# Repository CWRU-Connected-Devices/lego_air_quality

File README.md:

# LEGO Air Quality Monitor

An educational STEM kit developed by the Case Western Reserve University Institute for Smart, Secure and
Connected Systems (ISSACS). Participants build a working model of an optical air quality sensor using LEGO
bricks, custom electronics, and a Raspberry Pi Pico.

## What It Teaches

Real-world air quality monitors measure particulate matter (PM) by shining light through air and detecting
how much is scattered by particles. This kit builds a physical model of that principle: a LEGO brick
structure channels water vapor between a white LED and a photoreceptor. As vapor density changes, so does
the light reaching the sensor — just as particles would affect a real PM sensor. An 8-LED bar graph
displays the relative reading in real time.

## Repository Contents

- **`firmware/`** — MicroPython source code for the Raspberry Pi Pico
- **`legos/`** — 3D-printable LEGO-compatible brick designs (STL files + BrickLink Studio layout)
- **`pcb/`** — PCB design files (Eagle source, schematic PDF, Gerbers for fabrication)
- **`docs/`** — Documentation for kit builders, instructors, and participants
- **`images/`** — Reference photos used in documentation

## Attribution

This project is free to use and adapt under the MIT License. If you use these materials in your program,
we ask that you credit **CWRU ISSACS** and include our logo on participant-facing materials.

## License

MIT License — Copyright (c) 2021 Case Western Reserve University Institute for Smart, Secure and Connected
Systems. See [LICENSE](LICENSE) for details.

---

LEGO is a trademark of the LEGO Group, which does not sponsor, authorize, or endorse this project.

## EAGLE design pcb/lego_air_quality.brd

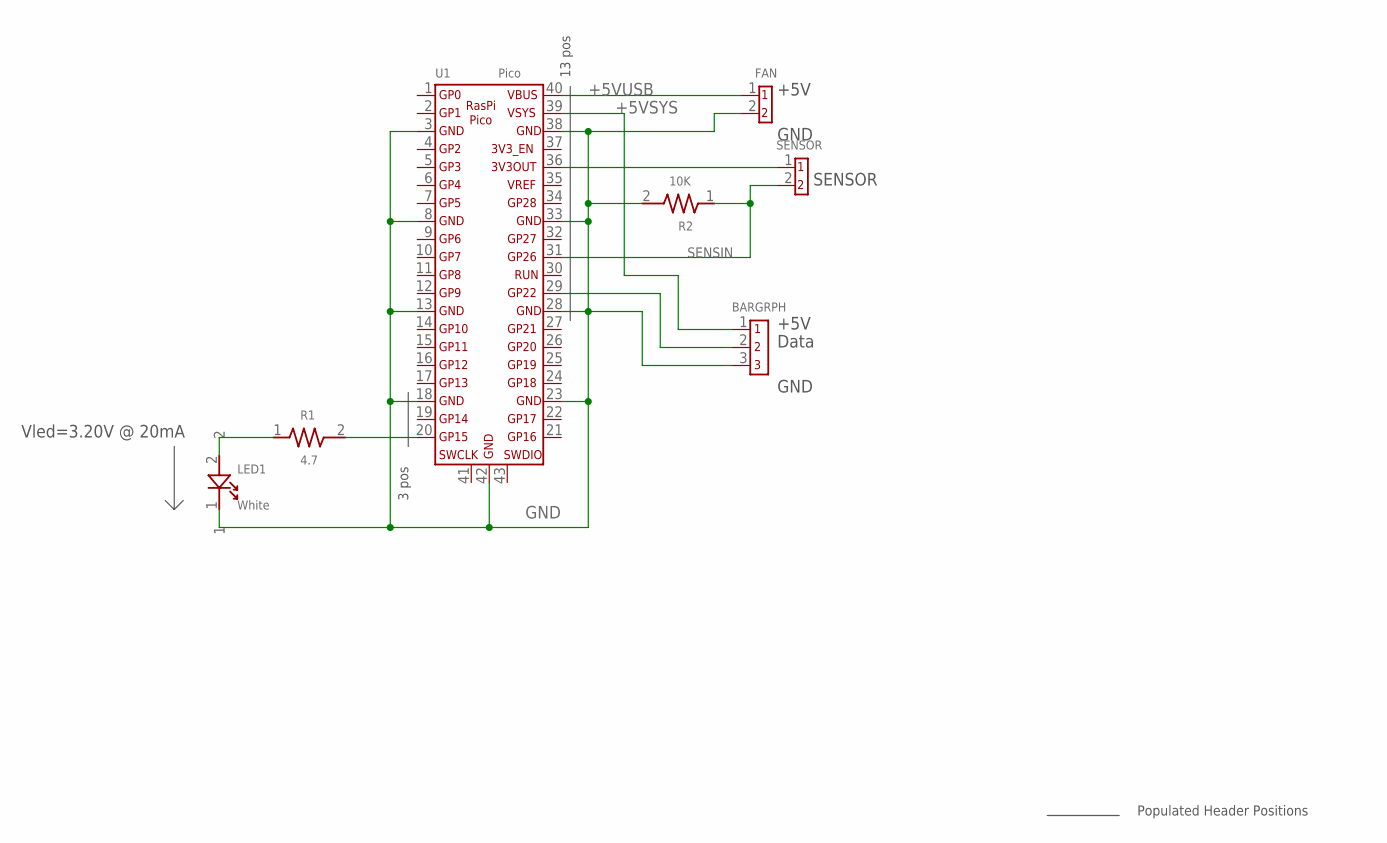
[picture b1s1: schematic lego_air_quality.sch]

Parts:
BARGRPH: 3PINBERG
FAN: 2PINBERG
LED1: White; LED5MM
R1: 4.7; R0_25W
R2: 10K; R0_25W
SENSOR: 2PINBERG
U1: Pico; RASPIPICO

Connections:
+5VSYS: BARGRPH.1, U1.39
+5VUSB: FAN.1, U1.40
GND: BARGRPH.3, FAN.2, LED1.1, R2.2, U1.3, U1.8, U1.13, U1.18, U1.23, U1.28, U1.33, U1.38, U1.42
unnamed: R1.2, U1.20
unnamed: LED1.2, R1.1
unnamed: SENSOR.1, U1.36
unnamed: BARGRPH.2, U1.29
SENSIN: R2.1, SENSOR.2, U1.31

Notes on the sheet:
GND
SENSOR
Data
+5V
Vled=3.20V @ 20mA
13 pos
3 pos
Populated Header Positions

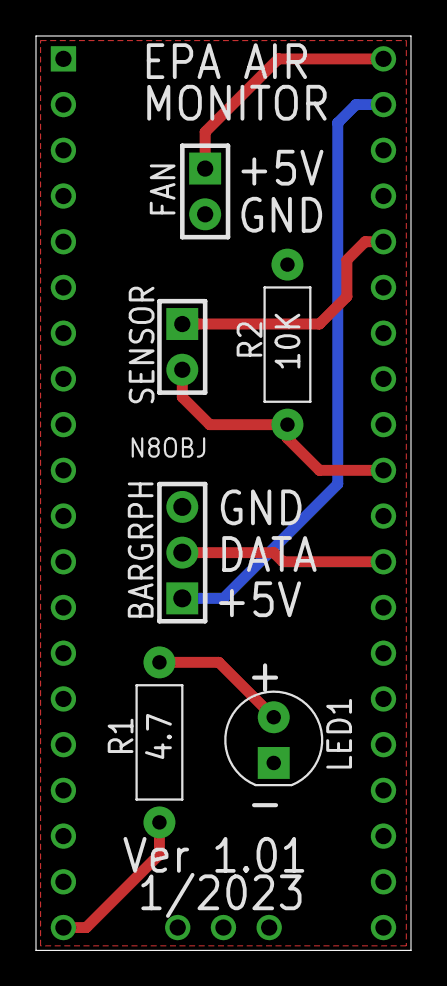
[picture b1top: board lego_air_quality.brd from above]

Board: 2 copper layers, 20.8 x 50.8 mm, 7 parts (0 on the bottom side), 8 nets.

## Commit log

2021-07-26 initial commit, added py script
2021-07-26 added micropython uf2 file
2021-08-11 finalization of repo
2021-08-11 finalization
2024-04-03 Adding files for custom PCB
2024-04-21 added new lego models
2024-05-29 Add files via upload
    Model for lego setup
2024-05-29 Copied over README.md
2024-05-29 Create images
2024-05-29 Create placeholder
2026-02-27 Adding gitignore with defaults
2026-02-27 Starting with MIT license
2026-02-27 Introducing Claude Code to the repo
2026-02-27 Cleaning up pico firmware
2026-02-28 First draft at making the README more general
2026-02-28 Updating CLAUDE.md to reflect current state better
2026-03-02 Cleaning up models directory and only including necessary files
2026-03-11 Clean up of readme and other docs
2026-03-11 Adding missing document
2026-03-11 Make it clear LEGO does not sponsor this project
2026-03-11 Markdown documentation for participant
2026-03-11 Instructor documentation
2026-03-27 Creating guides for kit builders
